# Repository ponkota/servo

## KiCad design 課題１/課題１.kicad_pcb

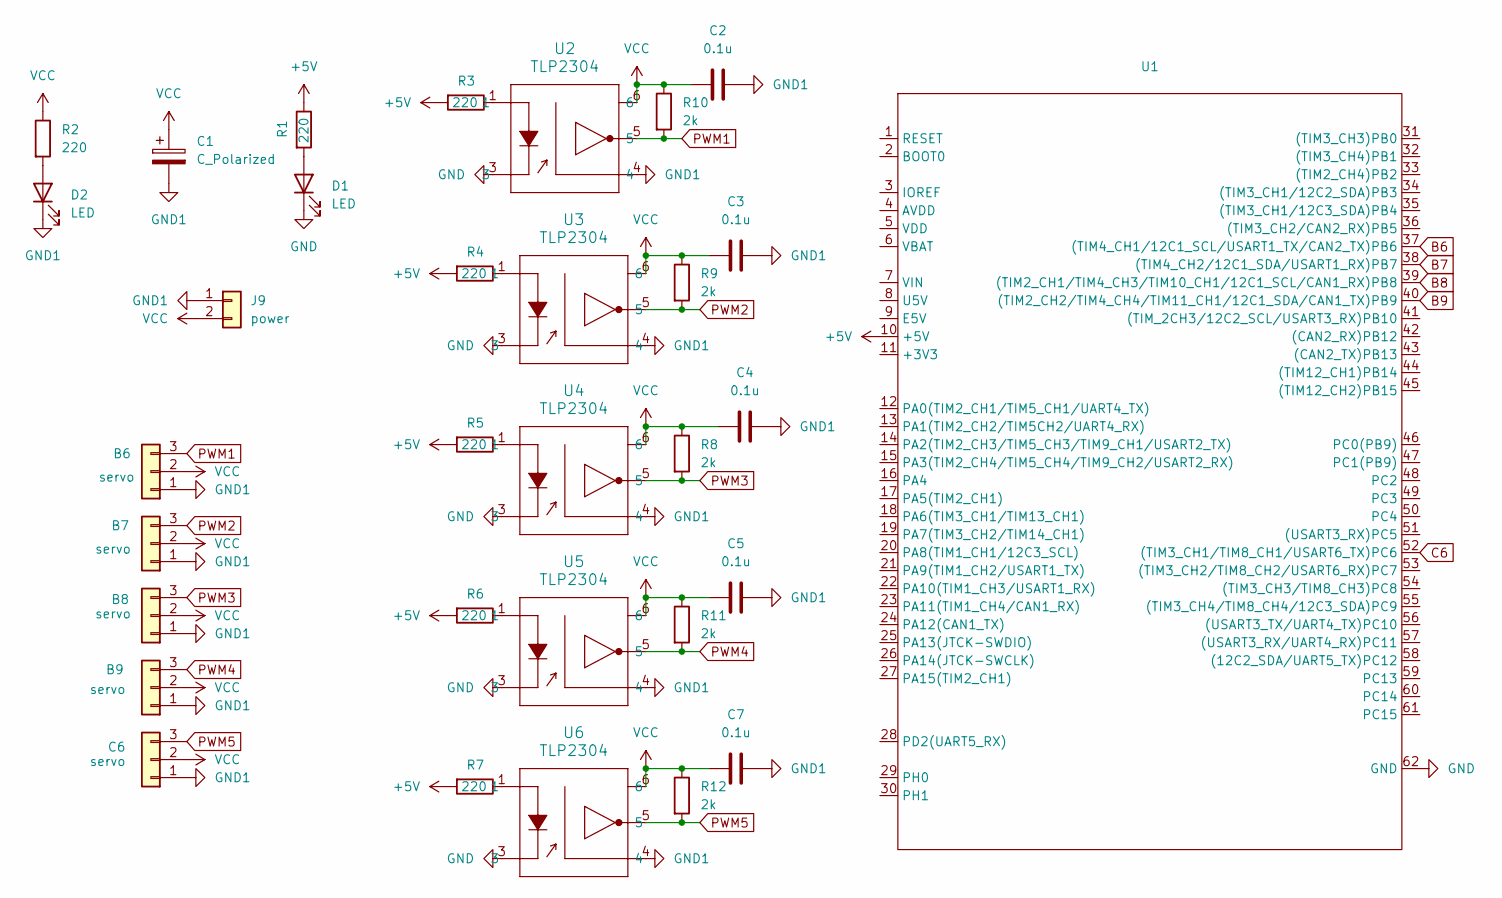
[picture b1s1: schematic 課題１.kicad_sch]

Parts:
B6, B7, B8, B9: servo; PinHeader_1x03_P2.54mm_Vertical
C1: C_Polarized; CP_Radial_D5.0mm_P2.00mm
C2, C3, C4, C5, C7: 0.1u; C_Disc_D3.0mm_W1.6mm_P2.50mm
C6: servo; PinSocket_1x03_P2.54mm_Vertical
D1, D2: LED; LED_D3.0mm
J9: power; AMASS_XT60PW-M_1x02_P7.20mm_Horizontal
R1, R2, R3, R4, R5, R6, R7: 220; R_Axial_DIN0207_L6.3mm_D2.5mm_P10.16mm_Horizontal
R8, R9, R10, R11, R12: 2k; R_Axial_DIN0207_L6.3mm_D2.5mm_P10.16mm_Horizontal
U1: STM32F446RE_Nucleo
U2, U3, U4, U5, U6: TLP2304; 5pin SO6_TOS

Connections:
+5V: R1.1, R3.2, R4.2, R5.2, R6.2, R7.2, U1.10 (+5V)
B6: U1.37 ((TIM4_CH1/12C1_SCL/USART1_TX/CAN2_TX)PB6)
B7: U1.38 ((TIM4_CH2/12C1_SDA/USART1_RX)PB7)
B8: U1.39 ((TIM2_CH1/TIM4_CH3/TIM10_CH1/12C1_SCL/C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)
B9: U1.40 ((TIM2_CH2/TIM4_CH4/TIM11_CH1/12C1_SDA/C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)
C6: U1.52 ((TIM3_CH1/TIM8_CH1/USART6_TX)PC6)
GND: D1.1 (K), U1.62 (GND), U2.3, U3.3, U4.3, U5.3, U6.3
GND1: B6.1, B7.1, B8.1, B9.1, C1.2, C2.2, C3.2, C4.2, C5.2, C6.1, C7.2, D2.1 (K), J9.1, U2.4, U3.4, U4.4, U5.4, U6.4
unnamed: D1.2 (A), R1.2
unnamed: D2.2 (A), R2.2
unnamed: R3.1, U2.1
unnamed: R4.1, U3.1
unnamed: R5.1, U4.1
unnamed: R6.1, U5.1
unnamed: R7.1, U6.1
PWM1: B6.3, R10.2, U2.5
PWM2: B7.3, R9.2, U3.5
PWM3: B8.3, R8.2, U4.5
PWM4: B9.3, R11.2, U5.5
PWM5: C6.3, R12.2, U6.5
VCC: B6.2, B7.2, B8.2, B9.2, C1.1, C2.1, C3.1, C4.1, C5.1, C6.2, C7.1, J9.2, R2.1, R8.1, R9.1, R10.1, R11.1, R12.1, U2.6, U3.6, U4.6, U5.6, U6.6

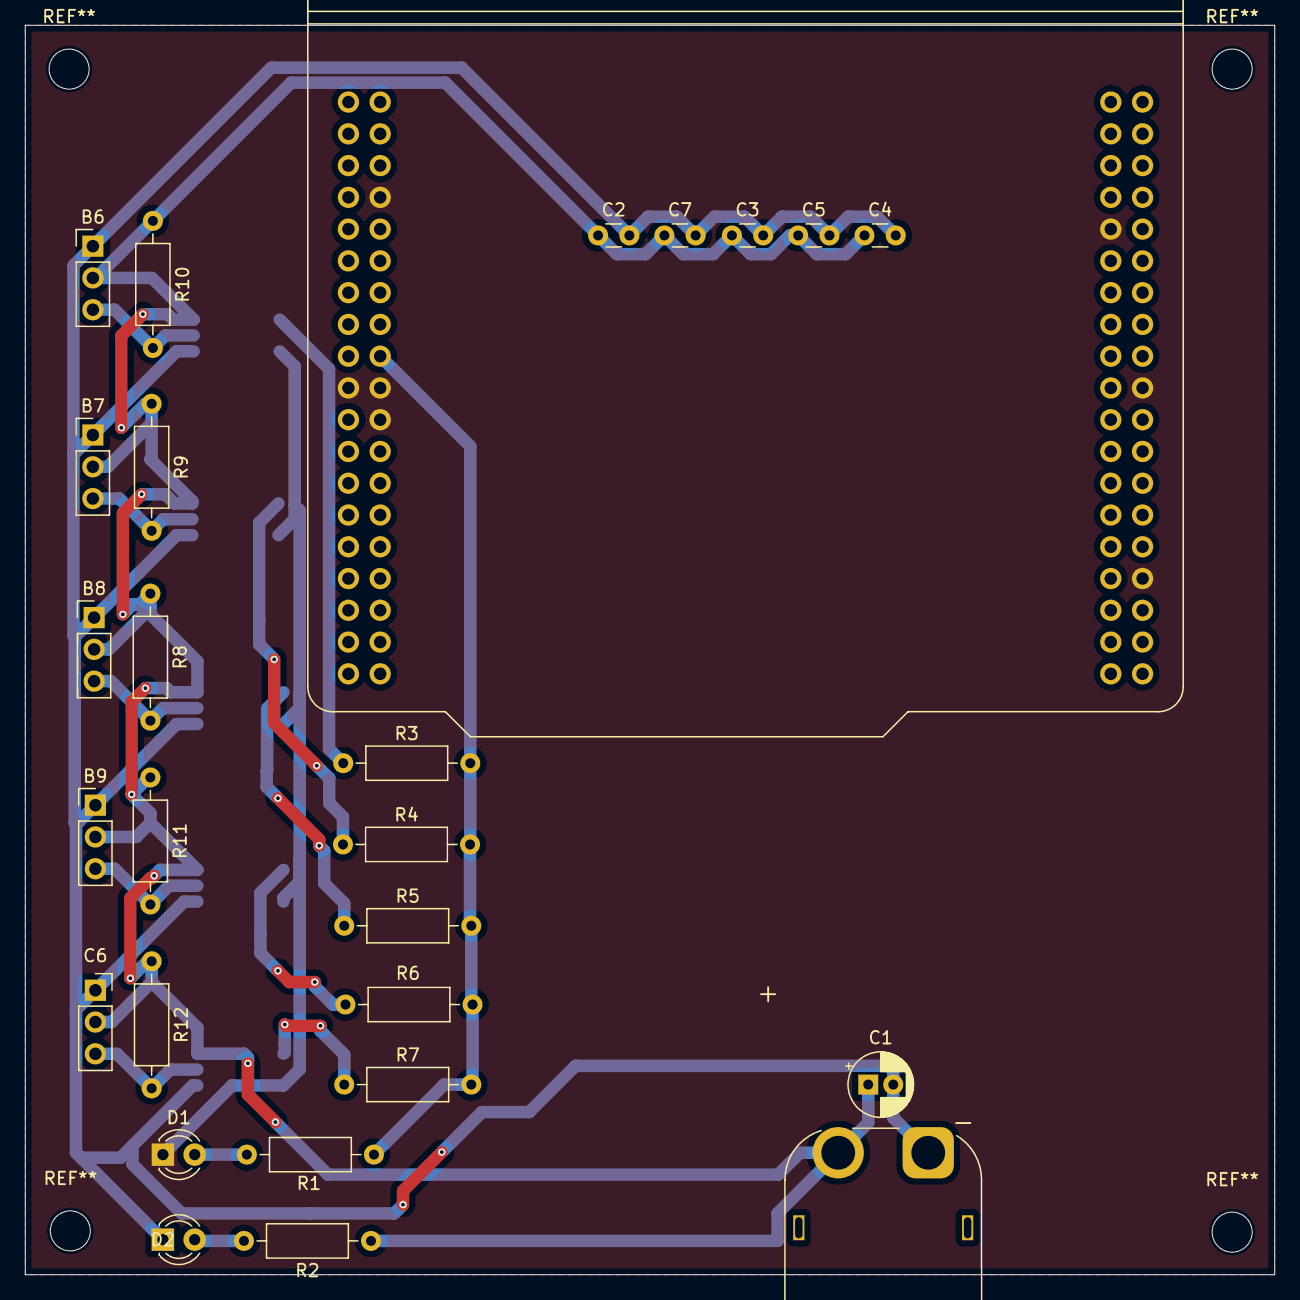
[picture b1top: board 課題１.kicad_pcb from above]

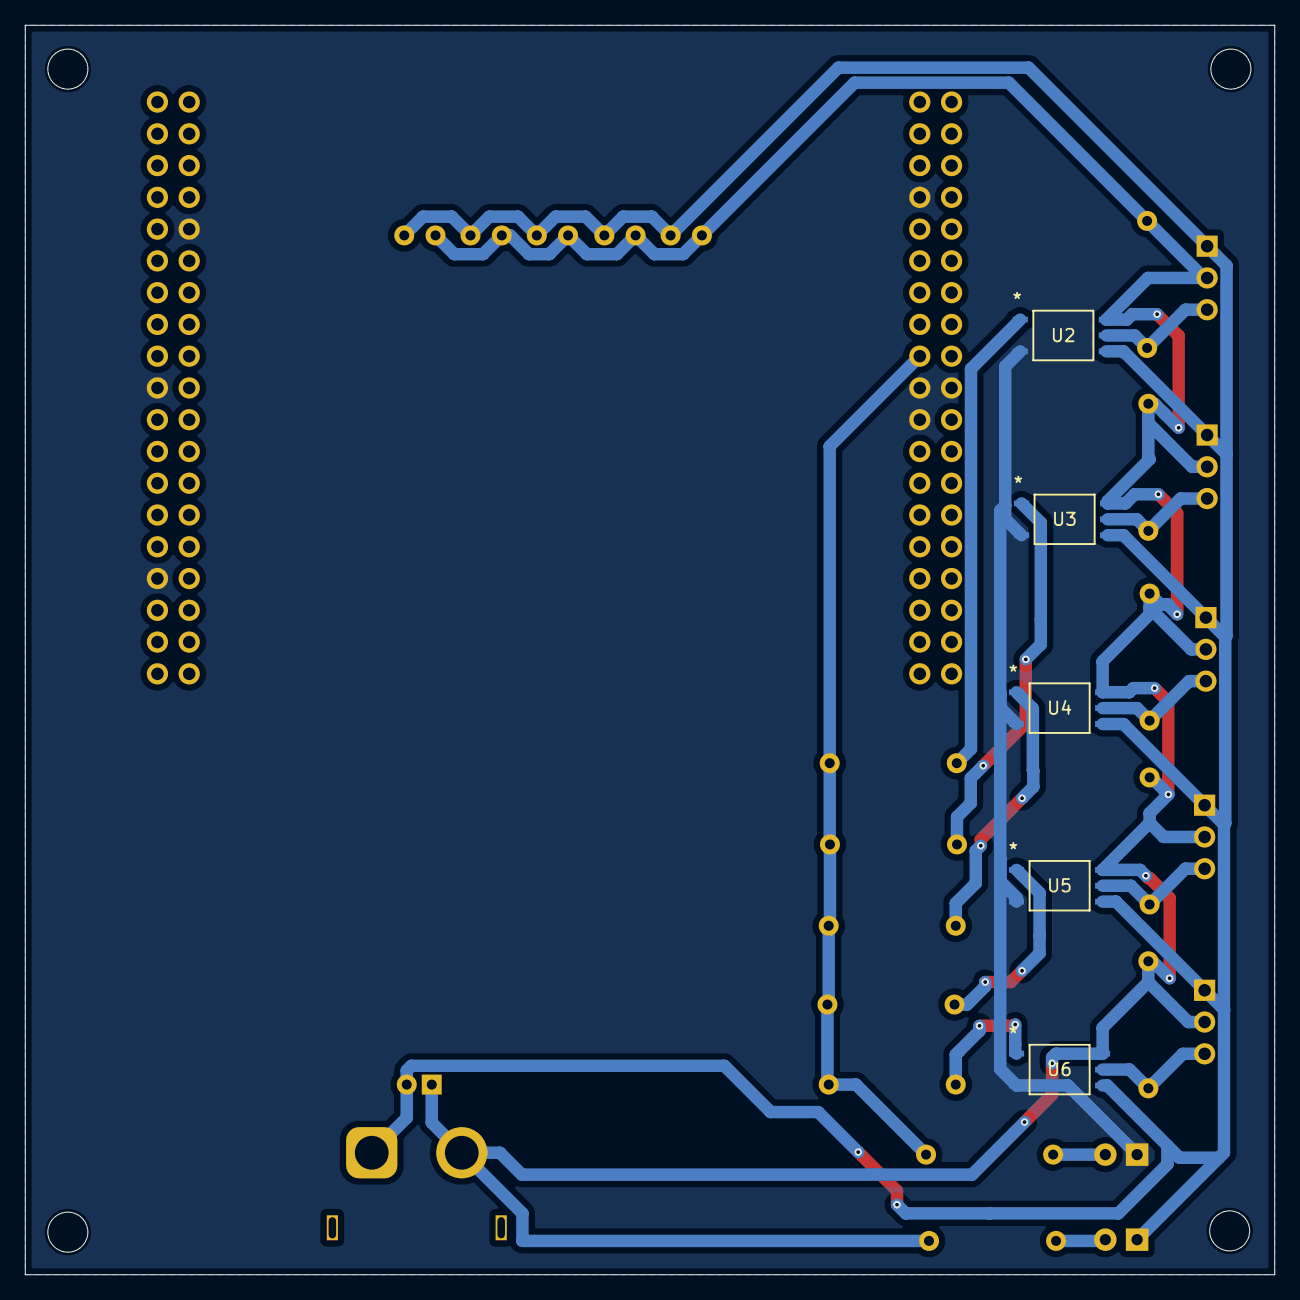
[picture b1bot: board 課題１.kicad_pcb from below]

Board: 2 copper layers, 99.9 x 99.9 mm, 32 parts (5 on the bottom side), 16 nets.
